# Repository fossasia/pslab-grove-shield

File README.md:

# PSLab Grove Shield

The Grove shield for the [Pocket Science Lab](https://pslab.io).

This repository hosts the schematics of the Grove Shield for the Pocket Science Lab open hardware platform (PSLab).

The goal of PSLab is to create an Open Source hardware device (open on all layers) and software applications that can be used for experiments by teachers, students and scientists. Our tiny pocket lab provides an array of instruments for doing science and engineering experiments. It provides functions of numerous measurement tools including an oscilloscope, a waveform generator, a frequency counter, a programmable voltage, current source and even a component to control robots with up to four servos. The website is at: https://pslab.io

The Grove open hardware project was started by Seeed Studio. The goal is to make it easier to connect, experiment, and simplify the prototyping process. No jumpers or soldering required. There are more than 300 Grove modules, covering a wide range of applications that can fulfill a variety of needs. The documentation for Grove shields is here: https://wiki.seeedstudio.com/Grove/

## Buy

* You can get a Pocket Science Lab device from the [FOSSASIA Shop](https://fossasia.com). The PSLab Grove shield will be available here in future as well.
* More resellers are listed on the [PSLab website](https://pslab.io/shop/).

## Communication

* Please also join us on the [PSLab Mailing List](https://groups.google.com/forum/#!forum/pslab-fossasia).

## Content of Repository

* **/docs**: Supplement materials, schematics as PDFs, images of PSLab
* **/schematics**: PCB layout of device

## Hardware Specifications

* [to be added]

## Development Platform

* [to be added]

## Features

* Grove pins
* Connect sensors easily

## Parts List

* [to be added]

### Dependencies

The shield needs the Pocket Science Lab hardware.

## License

The library is free and open source software licensed under the [Apache v2.0](LICENSE). The copyright is owned by FOSSASIA.

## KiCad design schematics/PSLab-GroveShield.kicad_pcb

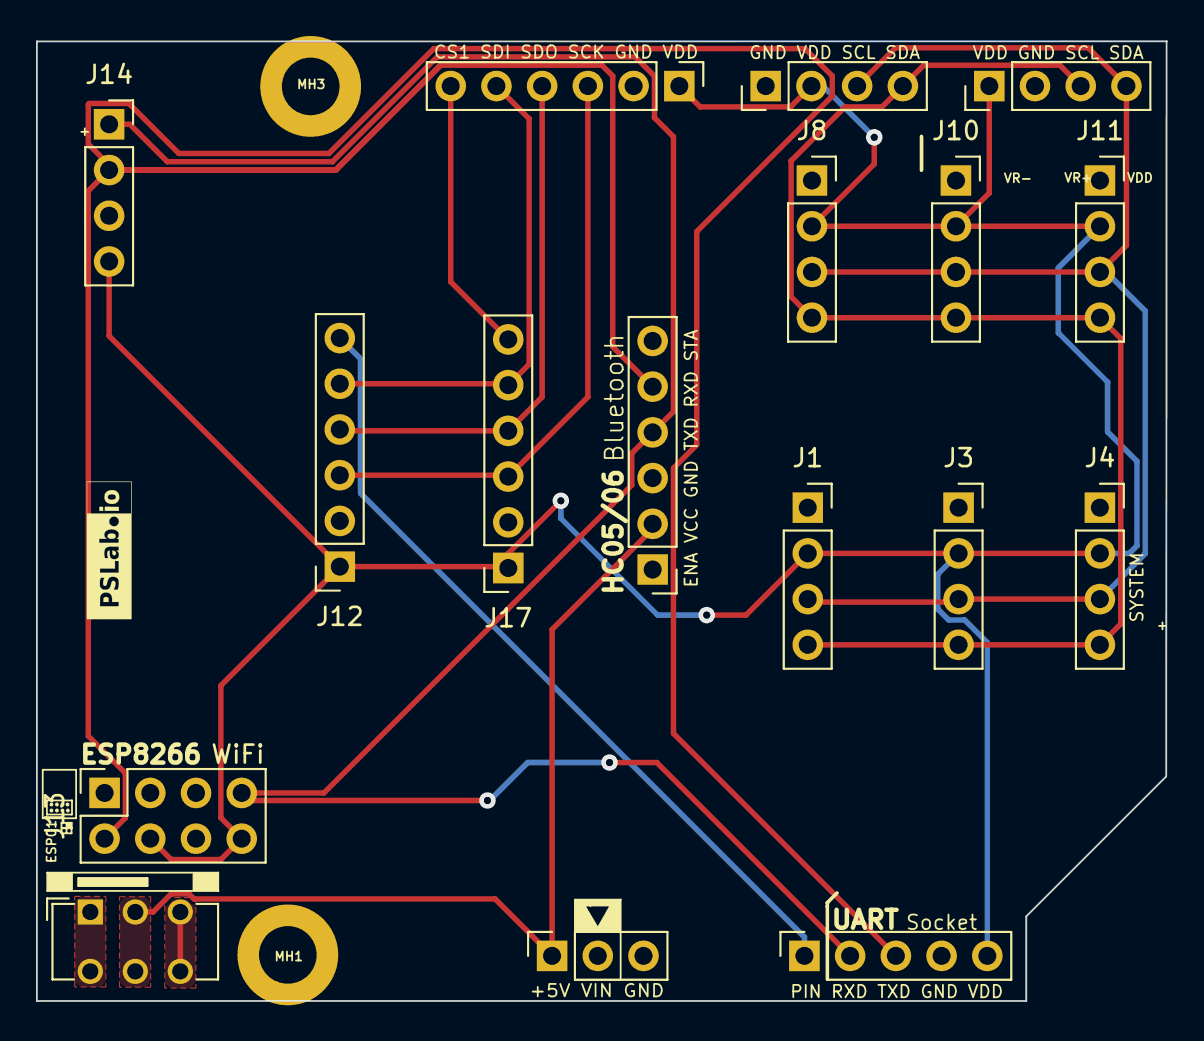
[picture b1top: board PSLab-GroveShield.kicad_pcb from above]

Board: 4 copper layers, 62.8 x 53.3 mm, 22 parts (0 on the bottom side), 14 nets.

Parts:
J1: I2C G6; PinSocket_1x04_P2.54mm_Vertical
J3: I2C G5; PinSocket_1x04_P2.54mm_Vertical
J4: I2C G4; PinSocket_1x04_P2.54mm_Vertical
J5: Bluetooth; Pin_Header_Straight_1x06_Pitch2.54mm
J6: I2C-1; Pin_Header_Straight_1x04_Pitch2.54mm
J7: UART/ESP; PinSocket_1x05_P2.54mm_Vertical
J8: I2C G3; PinSocket_1x04_P2.54mm_Vertical
J9: SPI Main; Pin_Header_Straight_1x06_Pitch2.54mm
J10: I2C G2; PinSocket_1x04_P2.54mm_Vertical
J11: I2C G1; PinSocket_1x04_P2.54mm_Vertical
J12: SPI G2; PinSocket_1x06_P2.54mm_Vertical
J13: ESP; PinSocket_2x04_P2.54mm_Vertical
J14: UART G1; PinSocket_1x04_P2.54mm_Vertical
J15: External Power; PinSocket_1x03_P2.54mm_Vertical
J16: I2C-2; Pin_Header_Straight_1x04_Pitch2.54mm
J17: SPI G1; PinSocket_1x06_P2.54mm_Vertical
MH1, MH3: M; MountingHole_3.2mm_M3_DIN965_Pad
S2: PSLab_Logo; PSLabDotIO
S4: PSLabDotIO_B; PSLabDotIO4000
S7: PSL_Logo
SW1: Power Route; SW_CuK_JS202011CQN_DPDT_Straight

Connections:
+5V: J5.2, J15.1, SW1.2, SW1.5
/SCL: J1.4, J3.4, J4.4, J6.4, J8.4, J10.4, J11.4, J16.3
/SDA: J1.3, J3.3, J4.3, J6.3, J8.3, J10.3, J11.3, J16.4
CS: J9.6, J17.6
ExP: SW1.3, SW1.6
GND: J1.1, J3.1, J4.1, J5.3, J6.1, J7.4, J8.1, J9.2, J10.1, J11.1, J12.2, J13.1, J14.3, J15.3, J16.2, J17.2, MH1.1, MH3.1
IOut: J7.1, J12.6
InP: SW1.1, SW1.4
RxD2: J5.5, J7.3, J13.2, J14.2
SCK: J9.3, J12.3, J17.3
SDI: J9.5, J12.5, J17.5
SDO: J9.4, J12.4, J17.4
TxD2: J5.4, J7.2, J13.7, J14.1
Vdd: J1.2, J3.2, J4.2, J6.2, J7.5, J8.2, J9.1, J10.2, J11.2, J12.1, J13.4, J13.8, J14.4, J16.1, J17.1

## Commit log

2016-06-23 Create gh-pages branch via GitHub
2016-06-23 Create CNAME
2016-07-06 files for the wordpess site added
2016-07-06 sql file for the wordpress database added
2016-07-06 Wordpress config file added
2016-07-06 add README.md
2016-07-07 Import the vietnamese pages
2016-07-07 Add xml file for the exported content
2020-05-30 init: initial commit
2020-05-30 docs: licence file
2020-09-13 feat: layout routing
2020-09-13 feat: layout routing (#3)
2020-09-15 Added pslab shield info and image
2020-09-15 imgage and docs
2020-10-01 feat: route updates and refactor
2020-10-01 feat: route updates (#5)
    * feat: layout routing
    * feat: route updates and refactor
2026-04-12 Update README.md by removing badges and links
    Removed outdated badges and updated communication channels.
